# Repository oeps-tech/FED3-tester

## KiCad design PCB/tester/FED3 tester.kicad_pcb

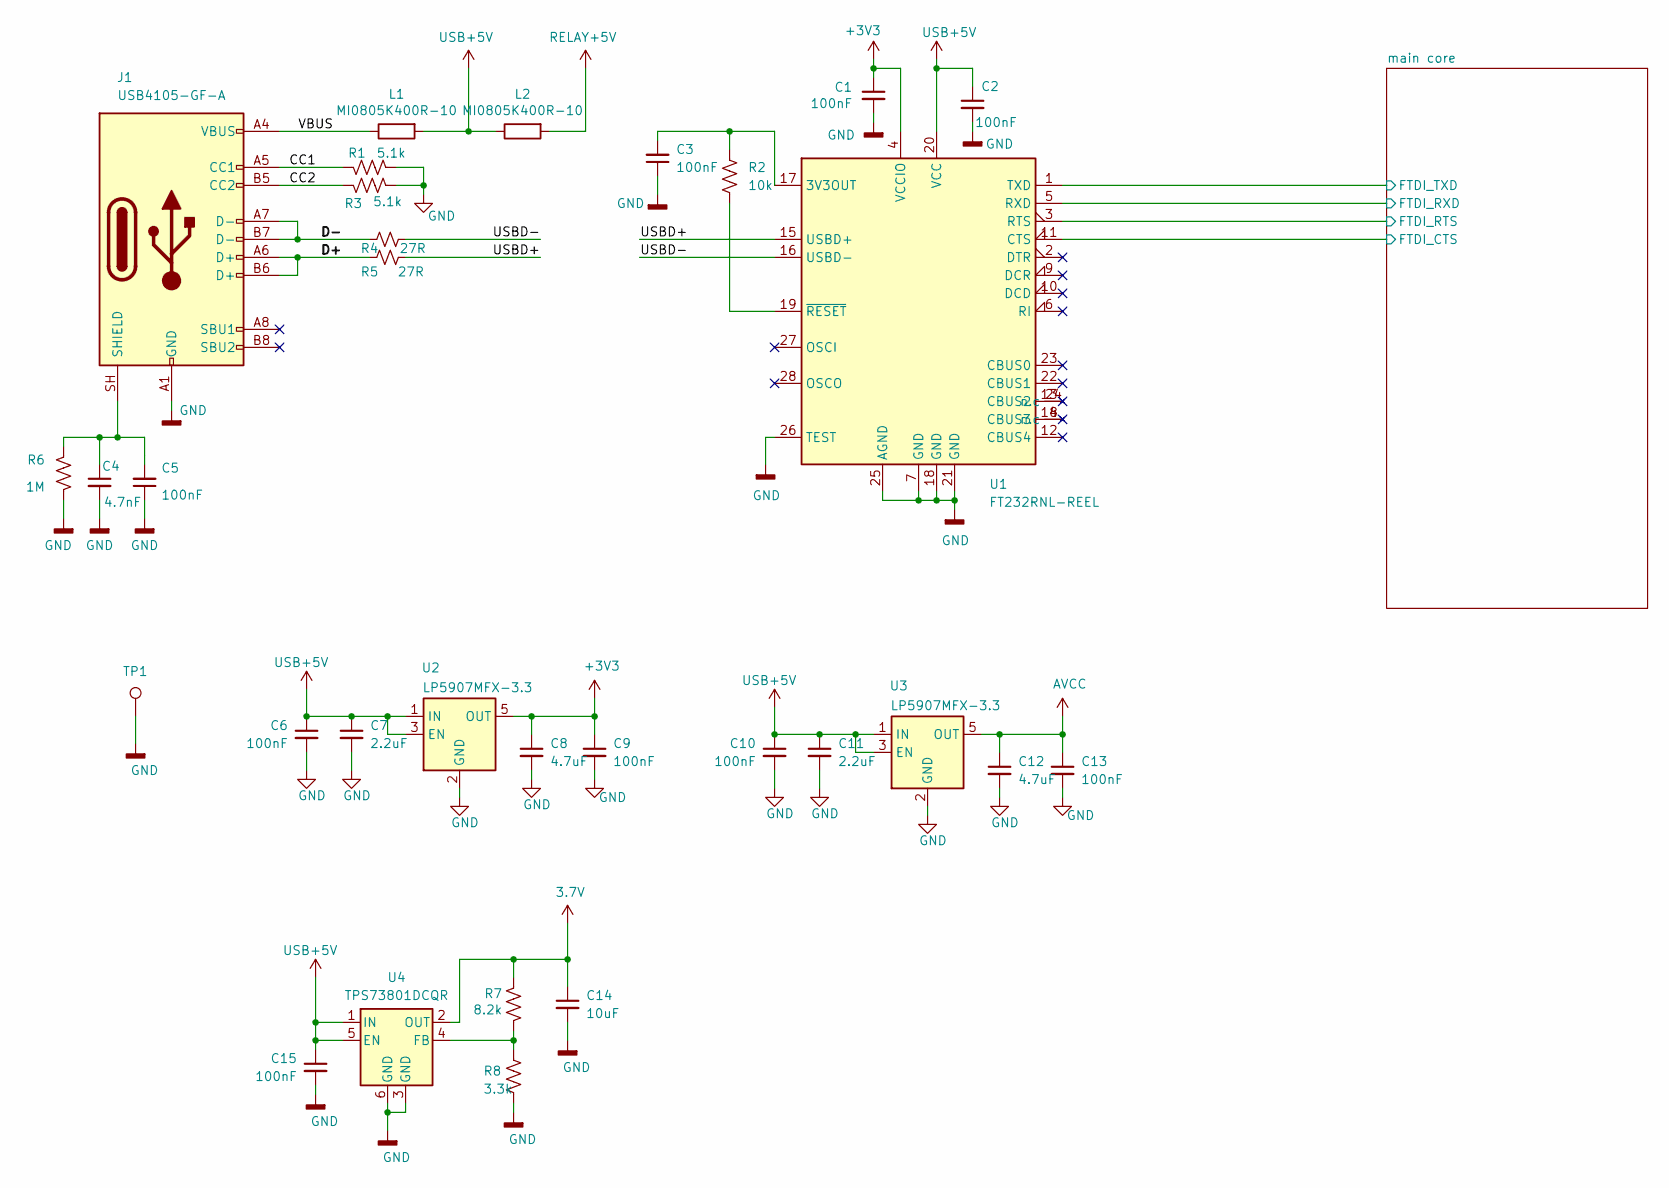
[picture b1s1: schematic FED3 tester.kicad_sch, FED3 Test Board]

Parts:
C1, C2, C3, C5, C6, C9, C10, C13, C15: 100nF; C_0402_1005Metric; Tolerance 10%; Voltage 50V; MPN CGA2B3X7R1H104K050BB
C4: 4.7nF; C_0402_1005Metric; Tolerance 10%; Voltage 100V; MPN 885012205084
C7, C11: 2.2uF; C_0603_1608Metric; Tolerance 10%; Voltage 25V; MPN GRM188R61E225KA12D
C8, C12: 4.7uF; C_0603_1608Metric; Tolerance 10%; Voltage 16V; MPN C1608X6S1C475K080AC
C14: 10uF; C_1206_3216Metric; Tolerance 10%; Voltage 25V; MPN GRM31CR71E106KA12L
J1: USB4105-GF-A; USB_C_Receptacle_GCT_USB4105-xx-A_16P_TopMnt_Horizontal; MPN USB4105-GF-A
L1, L2: MI0805K400R-10; R_0805_2012Metric; MPN MI0805K400R-10
R1, R3: 5.1k; R_0402_1005Metric; Tolerance 0.1%; MPN RT0402BRD075K1L
R2: 10k; R_0402_1005Metric; Tolerance 0.1%; MPN CPF0402B10KE1
R4, R5: 27R; R_0402_1005Metric; Tolerance 1%; MPN RMCF0402FT27R0
R6: 1M; R_0402_1005Metric; Tolerance 1%; MPN CRCW04021M00FKED
R7: 8.2k; R_0603_1608Metric; Tolerance 1%; MPN ERJ-3EKF8201V
R8: 3.3k; R_0402_1005Metric; Tolerance 1%; MPN ERJ-2RKF3301X
TP1: GND; PinHeader_1x01_P2.54mm_Vertical; MPN n.a
U1: FT232RNL-REEL; SSOP-28_5.3x10.2mm_P0.65mm; MPN FT232RNL-REEL
U2, U3: LP5907MFX-3.3; SOT-23-5; MPN LP5907MFX-3.3/NOPB
U4: TPS73801DCQR; SOT-223-6; MPN TPS73801DCQR

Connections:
3.7V: C14.1, R7.2, U4.2 (OUT); also elsewhere on the board
+3V3: C1.1, C8.1, C9.1, U1.4 (VCCIO), U2.5 (OUT); also elsewhere on the board
/CC1: J1.A5 (CC1), R1.1
/CC2: J1.B5 (CC2), R3.1
/D+: J1.A6 (D+), J1.B6 (D+), R5.2
/D-: J1.A7 (D-), J1.B7 (D-), R4.2
/USBD+: R5.1, U1.15 (USBD+)
/USBD-: R4.1, U1.16 (USBD-)
/VBUS: J1.A4 (VBUS), J1.A9 (VBUS), J1.B4 (VBUS), J1.B9 (VBUS), L1.1
/main core/FTDI_CTS: U1.11 (CTS); also elsewhere on the board
/main core/FTDI_RTS: U1.3 (RTS); also elsewhere on the board
/main core/FTDI_RXD: U1.5 (RXD); also elsewhere on the board
/main core/FTDI_TXD: U1.1 (TXD); also elsewhere on the board
AVCC: C12.1, C13.1, U3.5 (OUT); also elsewhere on the board
GND: C1.2, C2.2, C3.1, C4.2, C5.1, C6.2, C7.2, C8.2, C9.2, C10.2, C11.2, C12.2, C13.2, C14.2, C15.2, J1.A1 (GND), J1.A12 (GND), J1.B1 (GND), J1.B12 (GND), R1.2, R3.2, R6.1, R8.1, TP1.1 (1_1), U1.7 (GND), U1.18 (GND), U1.21 (GND), U1.25 (AGND), U1.26 (TEST), U2.2 (GND), U3.2 (GND), U4.3 (GND), U4.6 (GND); also elsewhere on the board
unnamed: C4.1, C5.2, J1.SH (SHIELD), R6.2
unnamed: C3.2, R2.1, U1.17 (3V3OUT)
unnamed: R2.2, U1.19 (~RESET)
unnamed: R7.1, R8.2, U4.4 (FB)
RELAY+5V: L2.2; also elsewhere on the board
USB+5V: C2.1, C6.1, C7.1, C10.1, C11.1, C15.1, L1.2, L2.1, U1.20 (VCC), U2.1 (IN), U2.3 (EN), U3.1 (IN), U3.3 (EN), U4.1 (IN), U4.5 (EN); also elsewhere on the board

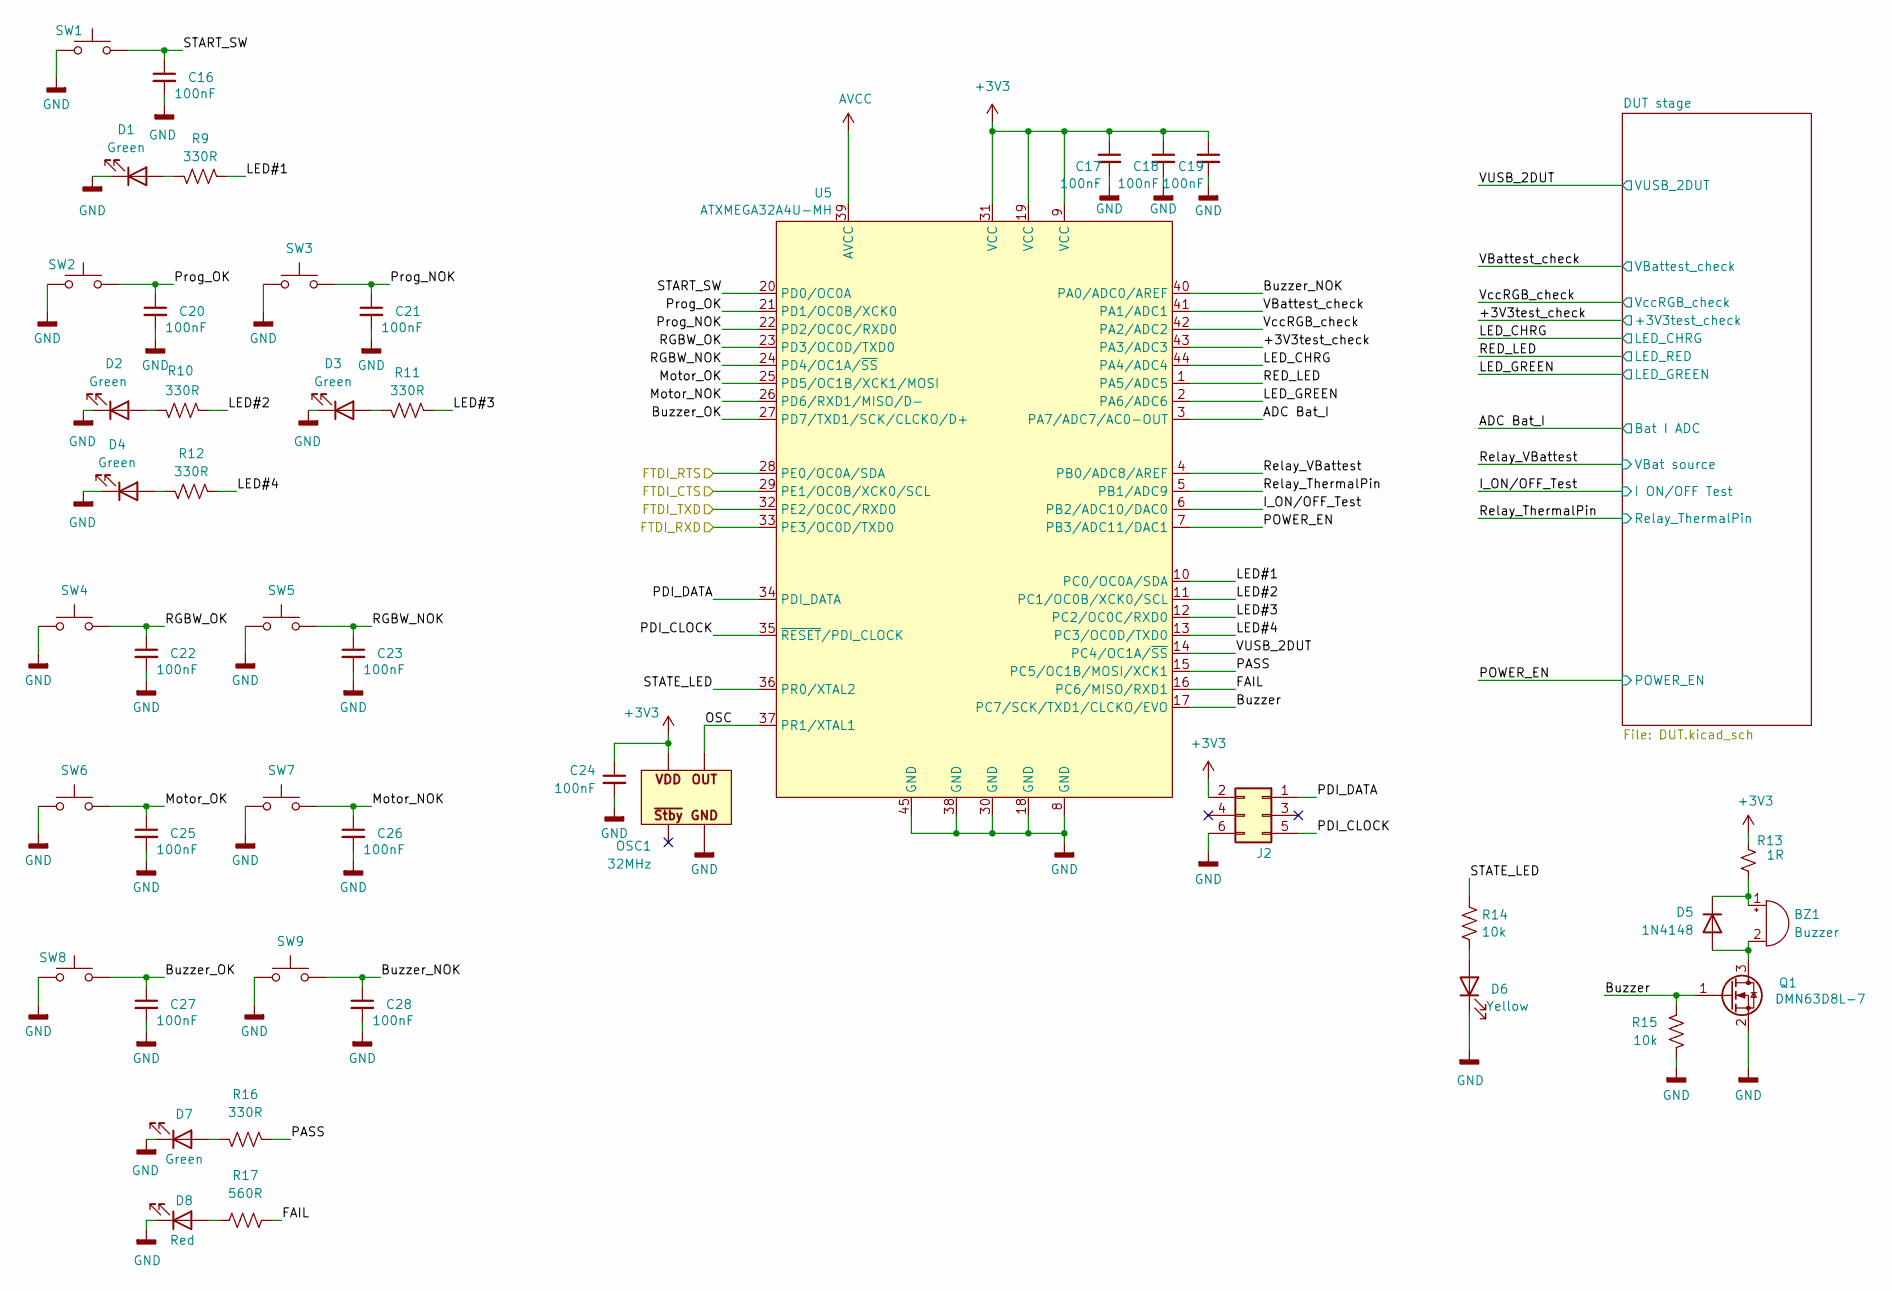
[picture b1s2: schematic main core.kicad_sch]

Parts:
BZ1: Buzzer; SMT-0540-T-9-R Buzzer; Voltage 3V; MPN CSS-0575A-SMT-TR
C16, C17, C18, C19, C20, C21, C22, C23, C24, C25, C26, C27, C28: 100nF; C_0402_1005Metric; Tolerance 10%; Voltage 50V; MPN CGA2B3X7R1H104K050BB
D1, D2, D3, D4, D7: Green; LED_0603_1608Metric; MPN LTST-C191KGKT
D5: 1N4148; D_SOD-123; MPN 1N4148WS-E3-18
D6: Yellow; LED_0603_1608Metric; MPN 5990040007F
D8: Red; LED_0603_1608Metric; MPN 5990010007F
J2: PR20203VBDN; PinHeader_2x03_P2.54mm_Vertical; MPN PR20203VBDN
OSC1: 32MHz; OSC; MPN DSC1001CI5-032.0000
Q1: DMN63D8L-7; SOT-23; MPN DMN63D8L-7
R9, R10, R11, R12, R16: 330R; R_0402_1005Metric; Tolerance 1%; MPN CRCW0402330RFKEDHP
R13: 1R; R_0402_1005Metric; Tolerance 1%; MPN CRCW04021R00FKEDHP
R14, R15: 10k; R_0402_1005Metric; Tolerance 0.1%; MPN CPF0402B10KE1
R17: 560R; R_0402_1005Metric; Tolerance 1%; MPN CRCW0402560RFKED
SW1, SW2, SW3, SW4, SW5, SW6, SW7, SW8, SW9: TL3305BF260QG; SW_SPST_TL3305B; MPN TL3305BF260QG
U5: ATXMEGA32A4U-MH; QFN-44-1EP_7x7mm_P0.5mm_EP5.2x5.2mm; MPN ATXMEGA32A4U-MHR

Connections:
+3V3: C17.1, C18.1, C19.1, C24.1, J2.2, OSC1.4 (VDD), R13.1, U5.9 (VCC), U5.19 (VCC), U5.31 (VCC); also elsewhere on the board
/main core/+3V3test_check: U5.43 (PA3/ADC3); also elsewhere on the board
/main core/ADC Bat_I: U5.3 (PA7/ADC7/AC0-OUT); also elsewhere on the board
/main core/Buzzer: Q1.1 (G), R15.2, U5.17 (PC7/SCK/TXD1/CLCKO/EVO)
/main core/Buzzer_NOK: C28.1, SW9.2, U5.40 (PA0/ADC0/AREF)
/main core/Buzzer_OK: C27.1, SW8.2, U5.27 (PD7/TXD1/SCK/CLCKO/D+)
/main core/FAIL: R17.2, U5.16 (PC6/MISO/RXD1)
/main core/FTDI_CTS: U5.29 (PE1/OC0B/XCK0/SCL); also elsewhere on the board
/main core/FTDI_RTS: U5.28 (PE0/OC0A/SDA); also elsewhere on the board
/main core/FTDI_RXD: U5.33 (PE3/OC0D/TXD0); also elsewhere on the board
/main core/FTDI_TXD: U5.32 (PE2/OC0C/RXD0); also elsewhere on the board
/main core/I_ON/OFF_Test: U5.6 (PB2/ADC10/DAC0); also elsewhere on the board
/main core/LED#1: R9.2, U5.10 (PC0/OC0A/SDA)
/main core/LED#2: R10.2, U5.11 (PC1/OC0B/XCK0/SCL)
/main core/LED#3: R11.2, U5.12 (PC2/OC0C/RXD0)
/main core/LED#4: R12.2, U5.13 (PC3/OC0D/TXD0)
/main core/LED_CHRG: U5.44 (PA4/ADC4); also elsewhere on the board
/main core/LED_GREEN: U5.2 (PA6/ADC6); also elsewhere on the board
/main core/Motor_NOK: C26.1, SW7.2, U5.26 (PD6/RXD1/MISO/D-)
/main core/Motor_OK: C25.1, SW6.2, U5.25 (PD5/OC1B/XCK1/MOSI)
/main core/OSC: OSC1.3 (OUT), U5.37 (PR1/XTAL1)
/main core/PASS: R16.2, U5.15 (PC5/OC1B/MOSI/XCK1)
/main core/PDI_CLOCK: J2.5, U5.35 (~RESET/PDI_CLOCK)
/main core/PDI_DATA: J2.1, U5.34 (PDI_DATA)
/main core/POWER_EN: U5.7 (PB3/ADC11/DAC1); also elsewhere on the board
/main core/Prog_NOK: C21.1, SW3.2, U5.22 (PD2/OC0C/RXD0)
/main core/Prog_OK: C20.1, SW2.2, U5.21 (PD1/OC0B/XCK0)
/main core/RED_LED: U5.1 (PA5/ADC5); also elsewhere on the board
/main core/RGBW_NOK: C23.1, SW5.2, U5.24 (PD4/OC1A/~SS)
/main core/RGBW_OK: C22.1, SW4.2, U5.23 (PD3/OC0D/TXD0)
/main core/Relay_ThermalPin: U5.5 (PB1/ADC9); also elsewhere on the board
/main core/Relay_VBattest: U5.4 (PB0/ADC8/AREF); also elsewhere on the board
/main core/START_SW: C16.1, SW1.2, U5.20 (PD0/OC0A)
/main core/STATE_LED: R14.2, U5.36 (PR0/XTAL2)
/main core/VBattest_check: U5.41 (PA1/ADC1); also elsewhere on the board
/main core/VUSB_2DUT: U5.14 (PC4/OC1A/~SS); also elsewhere on the board
/main core/VccRGB_check: U5.42 (PA2/ADC2); also elsewhere on the board
AVCC: U5.39 (AVCC); also elsewhere on the board
GND: C16.2, C17.2, C18.2, C19.2, C20.2, C21.2, C22.2, C23.2, C24.2, C25.2, C26.2, C27.2, C28.2, D1.1 (K), D2.1 (K), D3.1 (K), D4.1 (K), D6.1 (K), D7.1 (K), D8.1 (K), J2.6, OSC1.2 (GND), Q1.2 (S), R15.1, SW1.1, SW2.1, SW3.1, SW4.1, SW5.1, SW6.1, SW7.1, SW8.1, SW9.1, U5.8 (GND), U5.18 (GND), U5.30 (GND), U5.38 (GND), U5.45 (GND); also elsewhere on the board
unnamed: BZ1.1 (+), D5.1 (K), R13.2
unnamed: BZ1.2 (-), D5.2 (A), Q1.3 (D)
unnamed: D1.2 (A), R9.1
unnamed: D2.2 (A), R10.1
unnamed: D3.2 (A), R11.1
unnamed: D4.2 (A), R12.1
unnamed: D6.2 (A), R14.1
unnamed: D7.2 (A), R16.1
unnamed: D8.2 (A), R17.1

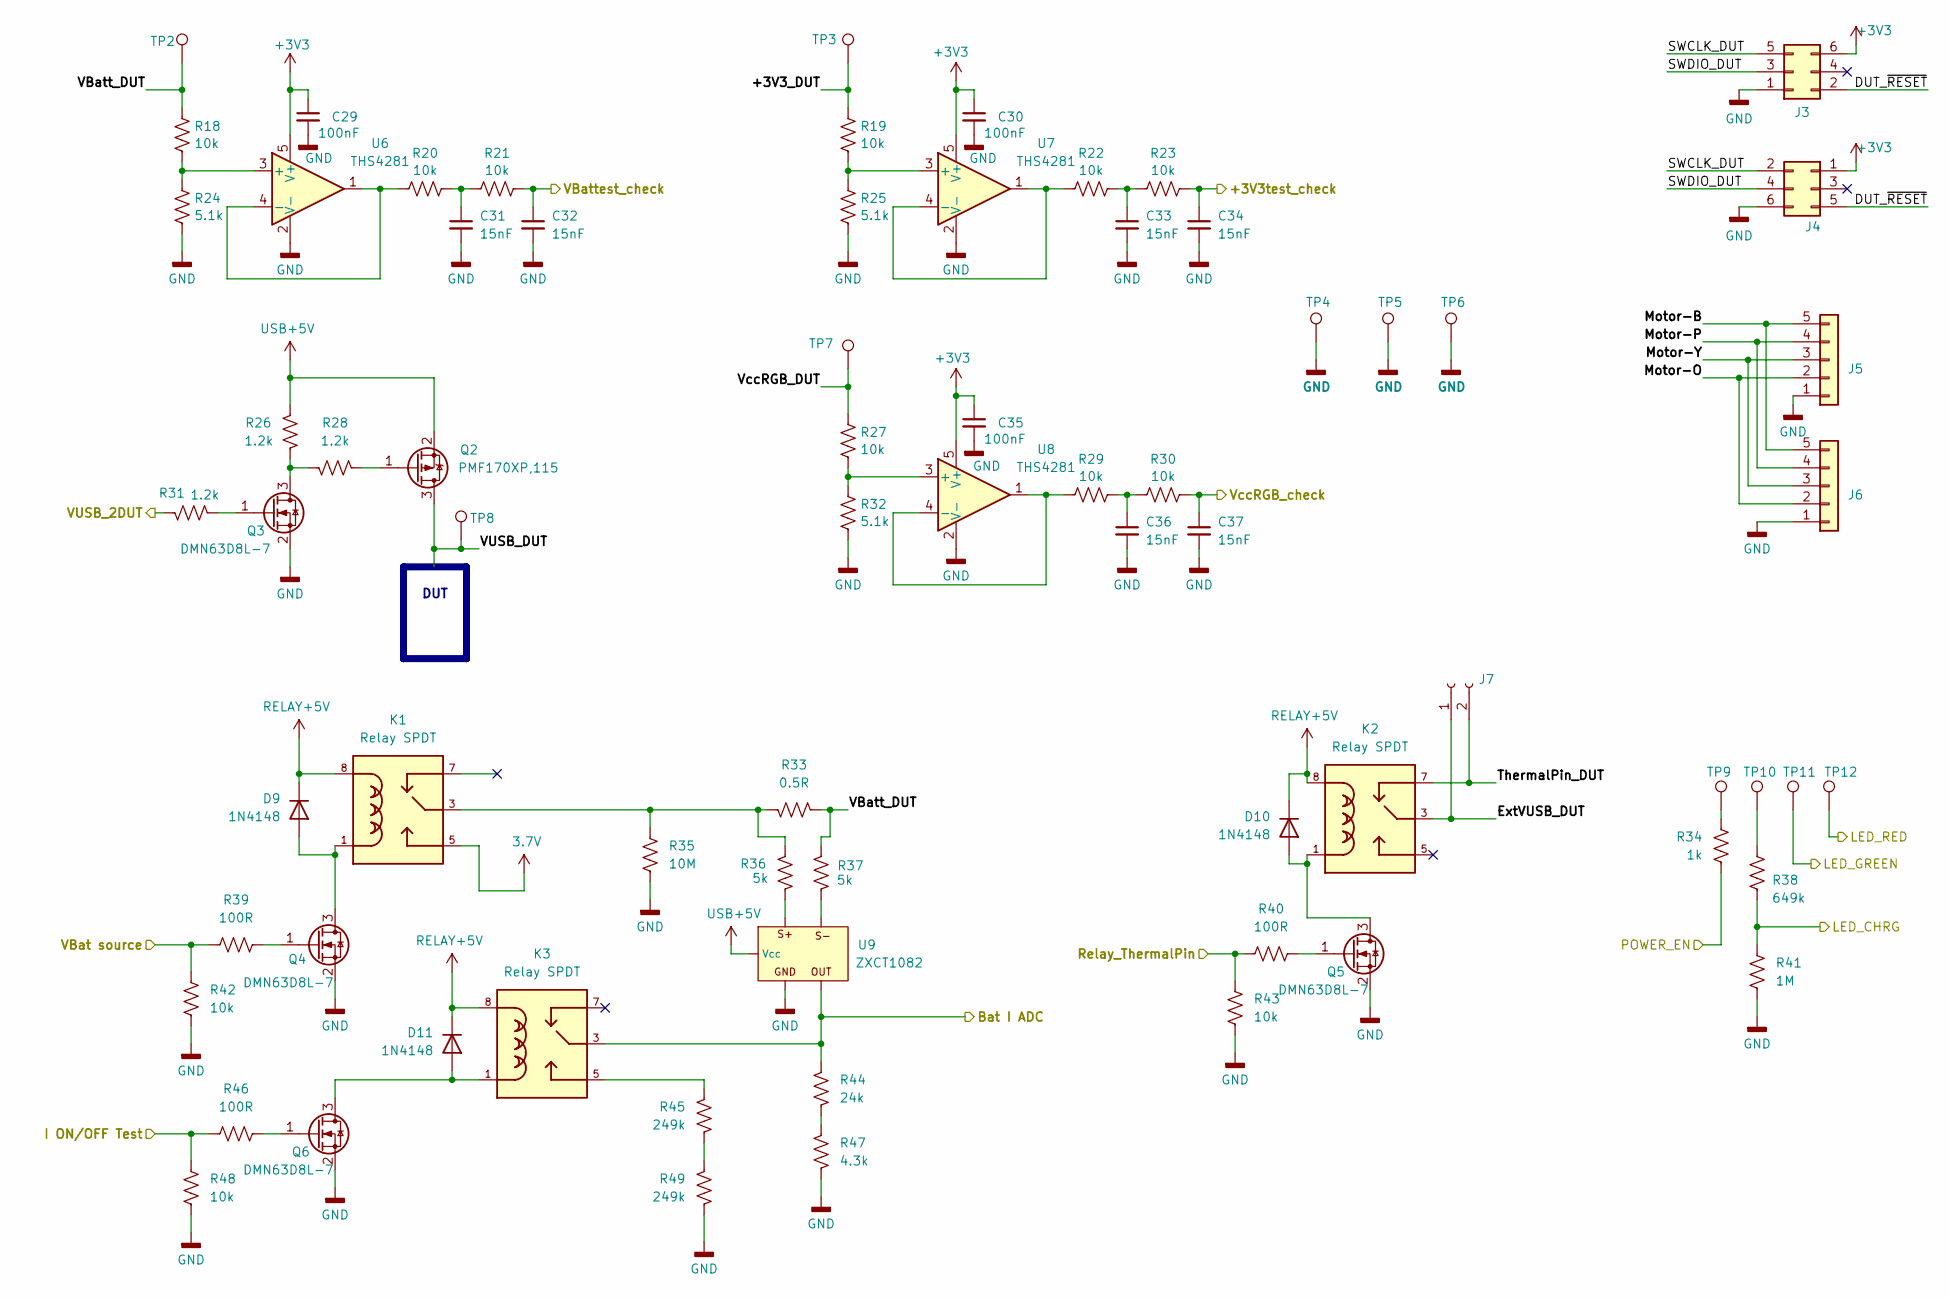
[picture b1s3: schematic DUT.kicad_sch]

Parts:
C29, C30, C35: 100nF; C_0402_1005Metric; Tolerance 10%; Voltage 50V; MPN CGA2B3X7R1H104K050BB
C31, C32, C33, C34, C36, C37: 15nF; C_0402_1005Metric; Tolerance 10%; Voltage 35V; MPN CGA2B3X7R1V153K050BB
D9, D10, D11: 1N4148; D_SOD-123; MPN 1N4148WS-E3-18
J3: 6pin_hd; PinHeader_2x03_to Probes; MPN n.a
J4: 61300621021; PinHeader_2x03_P2.54mm_Horizontal; MPN 61300621021
J5: PPTC051LFBN-RC; PinSocket_1x05_P2.54mm_Vertical; MPN PPTC051LFBN-RC
J6: 61300511021; PinSocket_1x05_P2.54mm_Horizontal; MPN 61300511021
J7: PPTC021LFBN-RC; PinSocket_1x02_P2.54mm_Vertical; MPN PPTC021LFBN-RC
K1, K2, K3: Relay SPDT; RELAY_1462042-8; MPN 1462042-8
Q2: PMF170XP,115; SOT-323_SC-70; MPN PMF170XP,115
Q3, Q4, Q5, Q6: DMN63D8L-7; SOT-23; MPN DMN63D8L-7
R18, R19, R20, R21, R22, R23, R27, R29, R30, R42, R43, R48: 10k; R_0402_1005Metric; Tolerance 0.1%; MPN CPF0402B10KE1
R24, R25, R32: 5.1k; R_0402_1005Metric; Tolerance 0.1%; MPN RT0402BRD075K1L
R26, R28, R31: 1.2k; R_0402_1005Metric; Tolerance 0.1%; MPN ERA-2AEB122X
R33: 0.5R; R_0805_2012Metric; Tolerance 1%; MPN RL1220S-R50-F
R34: 1k; R_0402_1005Metric; Tolerance 1%; MPN CRCW04021K00FKED
R35: 10M; R_0402_1005Metric; Tolerance 1%; MPN CRCW040210M0FKED
R36, R37: 5k; R_0402_1005Metric; Tolerance 0.1%; MPN PNM0402E5001BST1
R38: 649k; R_0402_1005Metric; Tolerance 1%; MPN ERJ-2RKF6493X
R39, R40, R46: 100R; R_0402_1005Metric; Tolerance 1%; MPN RCS0402100RFKED
R41: 1M; R_0402_1005Metric; Tolerance 1%; MPN CRCW04021M00FKED
R44: 24k; R_0402_1005Metric; Tolerance 1%; MPN ERJ-2RKF2402X
R45, R49: 249k; R_0402_1005Metric; Tolerance 1%; MPN RMCF0402FT249K
R47: 4.3k; R_0603_1608Metric; Tolerance 5%; MPN ERJ-3GEYJ432V
TP2: VBattest; Pin_D1.75mm; MPN n.a
TP3: +3V3test; Pin_D1.75mm; MPN n.a
TP4, TP5, TP6, TP9, TP10, TP11, TP12: GND; Pin_D1.75mm; MPN n.a
TP7: VccRGB; Pin_D1.75mm; MPN n.a
TP8: VUSBtest; Pin_D1.75mm; MPN n.a
U6, U7, U8: THS4281; SOT-23-5; MPN THS4281DBVT
U9: ZXCT1082; SOT-23-5; MPN ZXCT1082QE5TA

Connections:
3.7V: K1.5; also elsewhere on the board
+3V3: C29.1, C30.1, C35.1, J3.6, J4.1, U6.5 (V+), U7.5 (V+), U8.5 (V+); also elsewhere on the board
/main core/+3V3test_check: C34.1, R23.2; also elsewhere on the board
/main core/ADC Bat_I: K3.3, R44.1, U9.1 (OUT); also elsewhere on the board
/main core/DUT stage/+3V3_DUT: R19.2, TP3.1 (1_1)
/main core/DUT stage/DUT_~RESET: J3.2, J4.5
/main core/DUT stage/ExtVUSB_DUT: J7.1, K2.3
/main core/DUT stage/Motor-B: J5.5, J6.5
/main core/DUT stage/Motor-O: J5.2, J6.2
/main core/DUT stage/Motor-P: J5.4, J6.4
/main core/DUT stage/Motor-Y: J5.3, J6.3
/main core/DUT stage/SWCLK_DUT: J3.5, J4.2
/main core/DUT stage/SWDIO_DUT: J3.3, J4.4
/main core/DUT stage/ThermalPin_DUT: J7.2, K2.7
/main core/DUT stage/VBatt_DUT: R18.2, R33.2, R37.2, TP2.1 (1_1)
/main core/DUT stage/VUSB_DUT: Q2.3 (D), TP8.1 (1_1)
/main core/DUT stage/VccRGB_DUT: R27.2, TP7.1 (1_1)
/main core/I_ON/OFF_Test: R46.1, R48.2; also elsewhere on the board
/main core/LED_CHRG: R38.1, R41.2; also elsewhere on the board
/main core/LED_GREEN: TP11.1 (1_1); also elsewhere on the board
/main core/POWER_EN: R34.1; also elsewhere on the board
/main core/RED_LED: TP12.1 (1_1); also elsewhere on the board
/main core/Relay_ThermalPin: R40.1, R43.2; also elsewhere on the board
/main core/Relay_VBattest: R39.1, R42.2; also elsewhere on the board
/main core/VBattest_check: C32.1, R21.2; also elsewhere on the board
/main core/VUSB_2DUT: R31.2; also elsewhere on the board
/main core/VccRGB_check: C37.1, R30.2; also elsewhere on the board
GND: C29.2, C30.2, C31.2, C32.2, C33.2, C34.2, C35.2, C36.2, C37.2, J3.1, J4.6, J5.1, J6.1, Q3.2 (S), Q4.2 (S), Q5.2 (S), Q6.2 (S), R24.1, R25.1, R32.1, R35.1, R41.1, R42.1, R43.1, R47.2, R48.1, R49.1, TP4.1 (1_1), TP5.1 (1_1), TP6.1 (1_1), U6.2 (V-), U7.2 (V-), U8.2 (V-), U9.2 (GND); also elsewhere on the board
unnamed: C31.1, R20.2, R21.1
unnamed: C33.1, R22.2, R23.1
unnamed: C36.1, R29.2, R30.1
unnamed: D9.2 (A), K1.1, Q4.3 (D)
unnamed: D10.2 (A), K2.1, Q5.3 (D)
unnamed: D11.2 (A), K3.1, Q6.3 (D)
unnamed: K1.3, R33.1, R35.2, R36.2
unnamed: K3.5, R45.2
unnamed: Q2.1 (G), R28.2
unnamed: Q3.3 (D), R26.1, R28.1
unnamed: Q3.1 (G), R31.1
unnamed: Q4.1 (G), R39.2
unnamed: Q5.1 (G), R40.2
unnamed: Q6.1 (G), R46.2
unnamed: R34.2, TP9.1 (1_1)
unnamed: R38.2, TP10.1 (1_1)
unnamed: R44.2, R47.1
unnamed: R45.1, R49.2
unnamed: R18.1, R24.2, U6.3 (+)
unnamed: R20.1, U6.1, U6.4 (-)
unnamed: R19.1, R25.2, U7.3 (+)
unnamed: R22.1, U7.1, U7.4 (-)
unnamed: R27.1, R32.2, U8.3 (+)
unnamed: R29.1, U8.1, U8.4 (-)
unnamed: R36.1, U9.3 (S+)
unnamed: R37.1, U9.4 (S-)
RELAY+5V: D9.1 (K), D10.1 (K), D11.1 (K), K1.8, K2.8, K3.8; also elsewhere on the board
USB+5V: Q2.2 (S), R26.2, U9.5 (Vcc); also elsewhere on the board

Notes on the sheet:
DUT

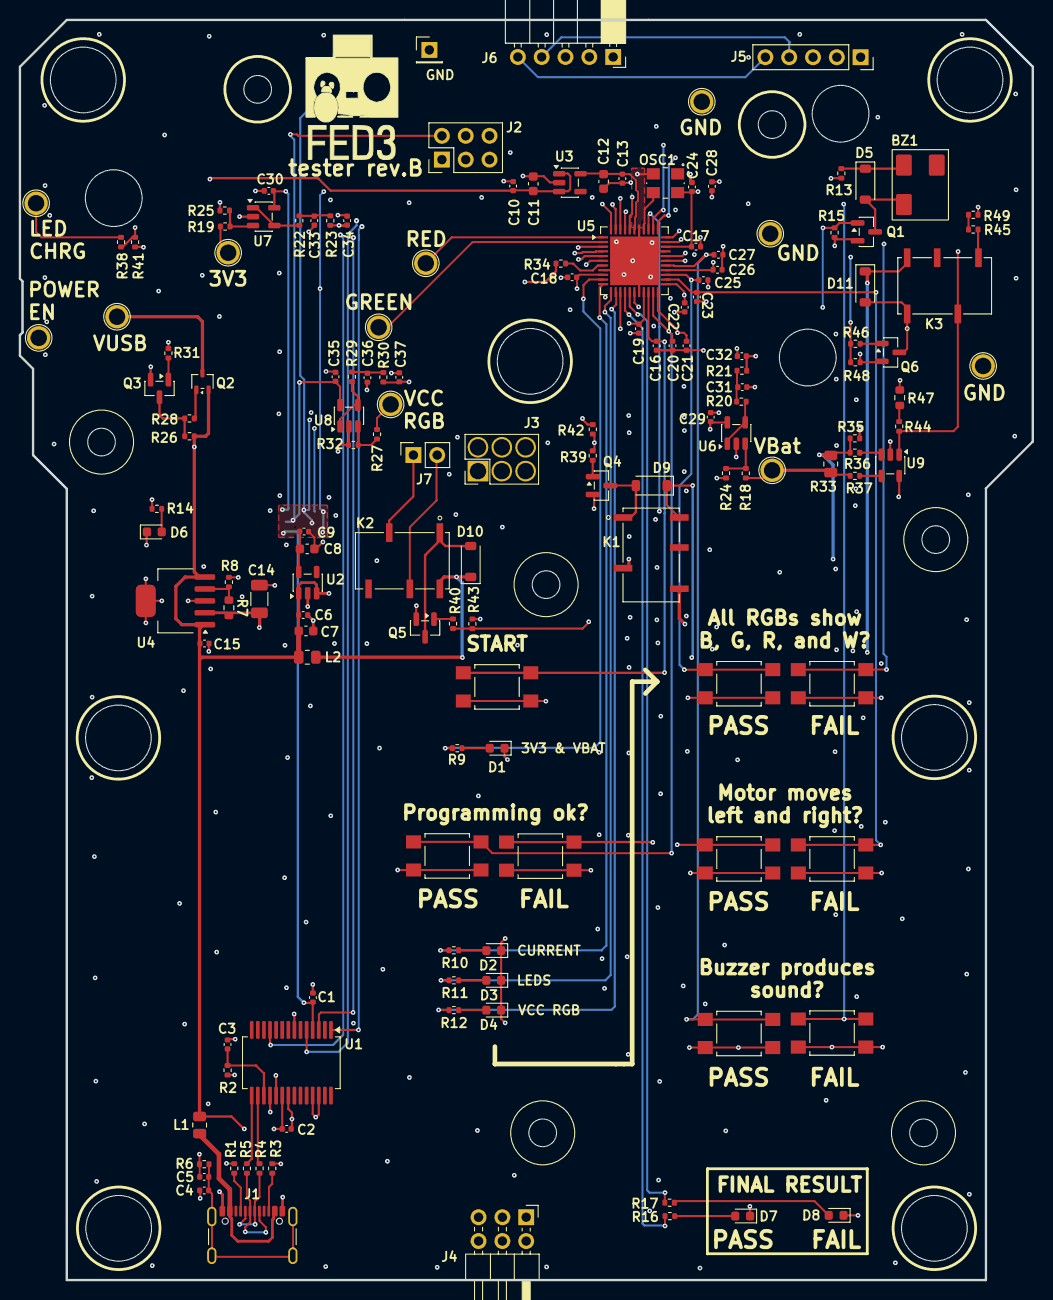
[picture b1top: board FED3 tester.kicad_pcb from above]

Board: 4 copper layers, 108.0 x 134.4 mm, 155 parts (0 on the bottom side), 101 nets.

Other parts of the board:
@HOLE6, @HOLE6#2, @HOLE6#3: MechHole_6.05mm
Ref**: Val**; MechHole_2.95mm
Ref**#2, Ref**#3, Ref**#4, Ref**#5: Val**; MechHole_2.95mm

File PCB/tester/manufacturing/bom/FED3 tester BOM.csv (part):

"#","Qty","Reference","Value","Tolerance","Footprint","TempCo","Voltage","Do Not Place","OEPSPN","MPN","Description"
"1","1","BZ1","Buzzer","","FED3_PCBLib:SMT-0540-T-9-R Buzzer","","3V","","OEPS100079","CSS-0575A-SMT-TR","OTHER:   BUZZER MAGNETIC 3V 5X5MM SMD   [CSS-0575A-SMT-TR] [SMD]"
"2","25","C1,C2,C3,C5,C6,C9,C10,C13,C15,C16,C17,C18,C19,C20,C21,C22,C23,C24,C25,C26,C27,C28,C29,C30,C35","100nF","10%","Capacitor_SMD:C_0402_1005Metric","X7R","50V","","OEPS010016","CGA2B3X7R1H104K050BB","CAPACITOR:   SMD CER 0402 100nF 50V ±10% X7R   [CGA2B3X7R1H104K050BB] [SMD]"
"3","1","C4","4.7nF","10%","Capacitor_SMD:C_0402_1005Metric","X7R","100V","","OEPS010017","885012205084","CAPACITOR:   SMD CER 0402 4.7nF 100V ±10% X7R   [885012205084] [SMD]"
"4","2","C7,C11","2.2uF","10%","Capacitor_SMD:C_0603_1608Metric","X5R","25V","","OEPS010075","GRM188R61E225KA12D","CAPACITOR:   SMD CER 0603 2.2uF 25V ±10% X5R (OEPS J30 006)   [GRM188R61E225KA12D] [SMD]"
"5","2","C8,C12","4.7uF","10%","Capacitor_SMD:C_0603_1608Metric","X6S","16V","","OEPS010018","C1608X6S1C475K080AC","CAPACITOR:   SMD CER 0603 4.7uF 16V ±10% X6S   [C1608X6S1C475K080AC] [SMD]"
"6","1","C14","10uF","10%","Capacitor_SMD:C_1206_3216Metric","X7R","25V","","OEPS010007","GRM31CR71E106KA12L","CAPACITOR:   SMD CER 1206 10uF 25V ±10% X7R   [GRM31CR71E106KA12L] [SMD]"
"7","6","C31,C32,C33,C34,C36,C37","15nF","10%","Capacitor_SMD:C_0402_1005Metric","X7R","35V","","OEPS010023","CGA2B3X7R1V153K050BB","CAPACITOR:   SMD CER 0402 15nF 35V ±10% X7R   [CGA2B3X7R1V153K050BB] [SMD]"
"8","5","D1,D2,D3,D4,D7","Green","","LED_SMD:LED_0603_1608Metric","","","","OEPS030005","LTST-C191KGKT","DIODE:   LED 0603 Green 571nm 20mA   [LTST-C191KGKT] [0603]"
"9","4","D5,D9,D10,D11","1N4148","","Diode_SMD:D_SOD-123","","","","OEPS030052","1N4148WS-E3-18","DIODE:   Standard 75V 150mA   [1N4148WX-TP] [SOD-323]"
"10","1","D6","Yellow","","LED_SMD:LED_0603_1608Metric","","","","OEPS030043","5990040007F","DIODE:   LED 0603 Yellow 590nm 20mA   [5990040007F] [0603]"
"11","1","D8","Red","","LED_SMD:LED_0603_1608Metric","","","","OEPS030044","5990010007F","DIODE:   LED 0603 Red 633nm 20mA   [5990010007F] [0603]"
"12","1","J1","USB4105-GF-A","","Connector_USB:USB_C_Receptacle_GCT_USB4105-xx-A_16P_TopMnt_Horizontal","","","","OEPS070105","USB4105-GF-A","CONNECTOR:   USB2.0 TYPE C 24P SMD R/A   [USB4105-GF-A] [SMD/TH]"
"13","1","J2","PR20203VBDN","","Connector_PinHeader_2.54mm:PinHeader_2x03_P2.54mm_Vertical","","","","OEPS070124","PR20203VBDN","CONNECTOR:   HEADER 2.54MM straight 2x3POS   [PR20203VBDN] [TH]"
"14","1","J4","61300621021","","Connector_PinHeader_2.54mm:PinHeader_2x03_P2.54mm_Horizontal","","","","OEPS070144","61300621021","CONNECTOR:   HEADER 2.54MM R/A 2x3POS   [61300621021] [TH]"
"15","1","J5","PPTC051LFBN-RC","","Connector_PinSocket_2.54mm:PinSocket_1x05_P2.54mm_Vertical","","","","OEPS070142","PPTC051LFBN-RC","CONNECTOR:   HEADER RCPT 2.54MM straight 1x5POS   [PPTC051LFBN-RC] [TH]"
"16","1","J6","61300511021","","Connector_PinSocket_2.54mm:PinSocket_1x05_P2.54mm_Horizontal","","","","OEPS070143","61300511021","CONNECTOR:   HEADER 2.54MM R/A 1x5POS   [61300511021] [TH]"
"17","1","J7","PPTC021LFBN-RC","","Connector_PinSocket_2.54mm:PinSocket_1x02_P2.54mm_Vertical","","","","OEPS070095","PPTC021LFBN-RC","CONNECTOR:   HEADER RCPT 2.54MM straight 1x2POS   [PPTC021LFBN-RC] [TH]"
"18","3","K1,K2,K3","Relay SPDT","","FED3_PCBLib:RELAY_1462042-8","","","","OEPS100078","1462042-8","OTHER:   RELAY SPDT 2A 5V TELECOM   [1462042-8] [SMD]"
"19","2","L1,L2","MI0805K400R-10","","Resistor_SMD:R_0805_2012Metric","","","","OEPS040003","MI0805K400R-10","INDUCTOR:   FERRITE BEAD SMD 40Ω 2A 50mΩ   [MI0805K400R-10] [0805]"
"20","1","OSC1","32MHz","","FED3_PCBLib:OSC","","","","OEPS080018","DSC1001CI5-032.0000","IC:   MEMS OSC XO 32MHZ CMOS 10ppm   [DSC1001CI5-032.0000] [4-SMD]"
"21","5","Q1,Q3,Q4,Q5,Q6","DMN63D8L-7","","Package_TO_SOT_SMD:SOT-23","","","","OEPS060013","DMN63D8L-7","TRANSISTOR:   MOSFET N-CH 30V 350mA   [DMN63D8L-7] [SOT23]"
"22","1","Q2","PMF170XP,115","","Package_TO_SOT_SMD:SOT-323_SC-70","","","","OEPS060012","PMF170XP,115","TRANSISTOR:   MOSFET P-CH 20V 1A   [PMF170XP,115] [SOT-323]"
"23","5","R1,R3,R24,R25,R32","5.1k","0.1%","Resistor_SMD:R_0402_1005Metric","","","","OEPS020203","RT0402BRD075K1L","RESISTOR:   SMD 0402 5.1kΩ ±0.1% 0.063W   [RT0402BRD075K1L] [SMD]"
"24","15","R2,R14,R15,R18,R19,R20,R21,R22,R23,R27,R29,R30,R42,R43,R48","10k","0.1%","Resistor_SMD:R_0402_1005Metric","","","","OEPS020043","CPF0402B10KE1","RESISTOR:   SMD 0402 10kΩ ±0.1% 0.063W   [CPF0402B10KE1] [SMD]"
"25","2","R4,R5","27R","1%","Resistor_SMD:R_0402_1005Metric","","","","OEPS020170","RMCF0402FT27R0","RESISTOR:   SMD 0402 27Ω ±1% 0.063W   [RMCF0402FT27R0] [SMD]"
"26","2","R6,R41","1M","1%","Resistor_SMD:R_0402_1005Metric","","","","OEPS020026","CRCW04021M00FKED","RESISTOR:   SMD 0402 1MΩ ±1% 0.063W   [CRCW04021M00FKED] [SMD]"
"27","1","R7","8.2k","1%","Resistor_SMD:R_0603_1608Metric","","","","OEPS020103","ERJ-3EKF8201V","RESISTOR:   SMD 0603 8.2kΩ ±1% 0.100W   [ERJ-3EKF8201V] [SMD]"
"28","1","R8","3.3k","1%","Resistor_SMD:R_0402_1005Metric","","","","OEPS020083","ERJ-2RKF3301X","RESISTOR:   SMD 0402 3.3kΩ ±1% 0.100W   [ERJ-2RKF3301X] [SMD]"
"29","5","R9,R10,R11,R12,R16","330R","1%","Resistor_SMD:R_0402_1005Metric","","","","OEPS020191","CRCW0402330RFKEDHP ","RESISTOR:   SMD 0402 330Ω ±1% 0.200W   [CRCW0402330RFKEDHP] [SMD]"
"30","1","R13","1R","1%","Resistor_SMD:R_0402_1005Metric","","","","OEPS020224","CRCW04021R00FKEDHP","RESISTOR:   SMD 0402 1Ω ±1% 0.200W   [CRCW04021R00FKEDHP] [SMD]"
"31","1","R17","560R","1%","Resistor_SMD:R_0402_1005Metric","","","","OEPS020193","CRCW0402560RFKED","RESISTOR:   SMD 0402 560Ω ±1% 0.063W   [CRCW0402560RFKED] [SMD]"
"32","3","R26,R28,R31","1.2k","0.1%","Resistor_SMD:R_0402_1005Metric","","","","OEPS020213","ERA-2AEB122X","RESISTOR:   SMD 0402 1.2kΩ ±0.1% 0.063W   [ERA-2AEB122X] [SMD]"
"33","1","R33","0.5R","1%","Resistor_SMD:R_0805_2012Metric","","","","OEPS020221","RL1220S-R50-F","RESISTOR:   SMD 0805 0.5Ω ±1% 1/3W    [RL1220S-R50-F] [SMD]"
"34","1","R34","1k","1%","Resistor_SMD:R_0402_1005Metric","","","","OEPS020027","CRCW04021K00FKED","RESISTOR:   SMD 0402 1kΩ ±1% 0.063W   [CRCW04021K00FKED] [SMD]"
"35","1","R35","10M","1%","Resistor_SMD:R_0402_1005Metric","","","","OEPS020211","CRCW040210M0FKED","RESISTOR:   SMD 0402 10MΩ ±1% 0.063W   [CRCW040210M0FKED] [SMD]"
"36","2","R36,R37","5k","0.1%","Resistor_SMD:R_0402_1005Metric","","","","OEPS020206","PNM0402E5001BST1","RESISTOR:   SMD 0402 5kΩ ±0.1% 0.050W   [PNM0402E5001BST1] [SMD]"
"37","1","R38","649k","1%","Resistor_SMD:R_0402_1005Metric","","","","OEPS020022","ERJ-2RKF6493X","RESISTOR:   SMD 0402 649kΩ ±1% 0.100W   [ERJ-2RKF6493X] [SMD]"
"38","3","R39,R40,R46","100R","1%","Resistor_SMD:R_0402_1005Metric","","","","OEPS020028","RCS0402100RFKED","RESISTOR:   SMD 0402 100Ω ±1% 0.250W   [RCS0402100RFKED] [SMD]"
"39","1","R44","24k","1%","Resistor_SMD:R_0402_1005Metric","","","","OEPS020048","ERJ-2RKF2402X","RESISTOR:   SMD 0402 24kΩ ±1% 0.100W   [ERJ-2RKF2402X] [SMD]"
"40","2","R45,R49","249k","1%","Resistor_SMD:R_0402_1005Metric","","","","OEPS020209","RMCF0402FT249K","RESISTOR:   SMD 0402 249kΩ ±1% 0.063W   [RMCF0402FT249K] [SMD]"
"41","1","R47","4.3k","5%","Resistor_SMD:R_0603_1608Metric","","","","OEPS020036","ERJ-3GEYJ432V","RESISTOR:   SMD 0603 4.3kΩ ±5% 0.100W   [ERJ-3GEYJ432V] [SMD]"
"42","9","SW1,SW2,SW3,SW4,SW5,SW6,SW7,SW8,SW9","TL3305BF260QG","","Button_Switch_SMD:SW_SPST_TL3305B","","","","OEPS100061","TL3305BF260QG","OTHER:   SWITCH TACTILE SPST-NO 0.05A 12V   [TL3305BF260QG] [SMD]"
"43","1","U1","FT232RNL-REEL","","Package_SO:SSOP-28_5.3x10.2mm_P0.65mm","","","","OEPS080093","FT232RNL-REEL","IC:   USB Interface IC USB to Serial UART   [FT232RNL-REEL] [SSOP-28]"
"44","2","U2,U3","LP5907MFX-3.3","","Package_TO_SOT_SMD:SOT-23-5","","","","OEPS080016","LP5907MFX-3.3/NOPB","IC:   LDO 3.3V 250mA   [LP5907MFX-3.3/NOPB] [SOT-23-5]"
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
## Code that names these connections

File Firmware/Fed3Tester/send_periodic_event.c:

#include "hwbp_core.h"

#include "buttons.h"
#include "analog_conversion.h"
#include "adc_calibration.h"
#include "adc_filter.h"
#include "execution.h"

extern buttons_t buttons;
extern AppRegs app_regs;

void send_periodic_event (void)
{
//  	for (uint8_t i = 0; i < ADC_QUANTITY; i++)
//  	{
//  		app_regs.REG_READINGS[i] = adc_get_uV(i);
//  	}

	// V_Vbat, V_VccRgb, V_3V3, V_LedCharge, V_LedRed, V_LedGreen, I_Vbat, SW_Start, SW_Prog, SW_Rgb, SW_Motor, SW_Buzzer, CurentState, PassFail
	
	app_regs.REG_READINGS[0] = get_V_Vbat();
	app_regs.REG_READINGS[1] = get_V_VccRgb();
	app_regs.REG_READINGS[2] = get_V_3V3();
	app_regs.REG_READINGS[3] = get_V_LedCharge();
	app_regs.REG_READINGS[4] = get_V_LedRed();
	app_regs.REG_READINGS[5] = get_V_LedGreen();
	app_regs.REG_READINGS[6] = get_I_Vbat();
		
	app_regs.REG_READINGS[7] = 0;
	app_regs.REG_READINGS[8] = 0;
	app_regs.REG_READINGS[9] = 0;
	app_regs.REG_READINGS[10] = 0;
	app_regs.REG_READINGS[11] = 0;
		
	if (buttons.start)      app_regs.REG_READINGS[7] = 1;
		
	if (buttons.prog_ok)    app_regs.REG_READINGS[8] = 1;
	if (buttons.prog_nok)   app_regs.REG_READINGS[8] = -1;
			
	if (buttons.rgb_ok)     app_regs.REG_READINGS[9] = 1;
	if (buttons.rgb_nok)    app_regs.REG_READINGS[9] = -1;
			
	if (buttons.motor_ok)   app_regs.REG_READINGS[10] = 1;
	if (buttons.motor_nok)  app_regs.REG_READINGS[10] = -1;
			
	if (buttons.buzzer_ok)  app_regs.REG_READINGS[11] = 1;
	if (buttons.buzzer_nok) app_regs.REG_READINGS[11] = -1;
	
	app_regs.REG_READINGS[12] = get_current_execution_state();
	app_regs.REG_READINGS[13] = get_pass_or_fail();

	core_func_send_event(ADD_REG_READINGS, true);
}

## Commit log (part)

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2026-05-15 Final details and production files
2026-05-15 Added addition al components
2026-05-22 Renamed BOM files
2026-05-28 Added the 3D design
2026-06-03 Update 1N4148 part numbers
    Replace obsolete 1N4148 :
    OEPS030017 -> OEPS030052
    1N4148WX-TP -> 1N4148WS-E3-18
2026-06-08 First firmware files
2026-06-11 Add ADC filtering, buttons, sound & state logic
2026-06-11 Refine analog reading comments and REG_READINGS
2026-06-15 Replace R13 100R with 1R and update BOM/metadata
